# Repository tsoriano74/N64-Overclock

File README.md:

# N64 Switchless Overclock 🎮

Salut les bidouilleurs et les makers ! Voici le petit PCB d’overclock que j’ai réalisé pour ma Nintendo 64 custom. Il utilise un **ATtiny45** et le firmware **ManCloud**, avec le bouton RESET pour sélectionner le mode et une LED bicolore pour le repérer.

Je partage les sources KiCad, les fichiers de fabrication, les photos et surtout la méthode de flash avec un **ESP32 utilisé comme programmateur ISP lent**. C’est ce qui nous a permis de contourner les soucis rencontrés avec l’adaptateur USBasp après le changement d’horloge de l’ATtiny.

## À quoi sert cette carte ?

L’**overclock**, c’est faire fonctionner le processeur de la console plus vite que son réglage habituel. Cela peut améliorer la fluidité de certains jeux, mais le résultat varie d’un jeu et d’une console à l’autre.

Le mot **switchless** signifie « sans interrupteur supplémentaire » : on utilise le bouton RESET déjà présent sur la N64 pour choisir le mode. La petite puce **ATtiny45** lit ce bouton et commande les signaux de sélection du processeur. Le programme qui lui dit quoi faire s’appelle le **firmware** ; ici, c’est celui de ManCloud.

### Comment changer de mode ?

1. Un appui court sert à réinitialiser la console, comme d’habitude.
2. Un appui long permet de changer le mode sélectionné, indiqué par la LED à deux couleurs.
3. Il faut ensuite **éteindre puis rallumer la console** pour appliquer le nouveau réglage.

Les nombres ×1,5 et ×2 sont des multiplicateurs de l’horloge de base. **×2 ne veut pas dire que la console devient deux fois plus rapide que d’origine** : son réglage habituel est déjà ×1,5.

### La version du programme utilisée

Le firmware choisi est la variante **ATtiny45, multiplicateur maximal ×2, LED à cathode commune**, compilée avec `make tiny45_CC`. Son fichier s’appelle `n64_overclock_t45_2_0X_CC.hex`. Un appui court conserve la fonction RESET ; un appui long fait défiler les modes. Après sélection, il faut **éteindre puis rallumer la console** pour appliquer le multiplicateur, comme l’indique [ManCloud](https://github.com/ManCloud/n64_overclock).

Le mode standard est ×1,5 et l’autre mode est ×2. Les performances et la stabilité dépendent de la console, de son refroidissement et du jeu. La couleur de la LED indique un choix ; pour confirmer la vitesse réellement obtenue, il faut une mesure ou un test de performances (un « benchmark »).

## La carte

## Programmer la carte : commencez ici

**Flasher** signifie copier un programme dans une puce. Il y a ici deux programmes différents :

| Programme | Où le charger ? | À quoi sert-il ? |
|---|---|---|
| Le sketch `ESP32_AVR_ISP.ino` | Dans l’ESP32, avec Arduino IDE | Transformer l’ESP32 en outil pour programmer l’ATtiny |
| Le firmware ManCloud au format `.hex` | Dans l’ATtiny45 de la carte overclock | Faire fonctionner le mod une fois installé dans la N64 |

Pendant la programmation, le chemin est : **ordinateur → câble USB → ESP32 → six fils → carte overclock**. L’ESP32 sert seulement à préparer la carte : il ne reste pas dans la console.

👉 **[Guide complet : Arduino IDE, ESP32, câblage, AVRDUDE et fusibles](docs/FLASH-ESP32.md)**

Le **sketch** (programme Arduino) [pour l’ESP32](programming/ESP32_AVR_ISP/ESP32_AVR_ISP.ino) a été retrouvé dans le fichier utilisé pour le projet. Il utilise **STK500v1**, le langage attendu par l’outil de transfert, à **19 200 bauds**. Il envoie les données à l’ATtiny avec une horloge lente d’environ **10 kHz**, adaptée à son réglage. Ces nombres sont déjà renseignés dans le guide et le sketch. Le guide distingue bien le firmware à charger dans l’ATtiny du sketch à charger dans l’ESP32.

**La dernière étape change le rôle d’une patte de l’ATtiny pour que le bouton RESET puisse servir au mod. Ensuite, on ne peut plus reprogrammer la puce avec ce même branchement ESP32.** C’est le réglage `HFUSE = 0x5F` : il faut le faire uniquement à la fin, après toutes les vérifications. Le guide explique cet ordre et la méthode particulière nécessaire pour revenir en arrière.

## Repères du PCB

Les **pastilles** sont les petites surfaces métalliques où souder les fils. Les inscriptions blanches sur la carte sont la **sérigraphie**. Le tableau ci-dessous indique où vont ces pastilles dans les fichiers KiCad fournis.

- **GND** : la masse, le point commun de référence électrique du montage.
- **3,3 V** : l’alimentation de la carte pendant la programmation.
- **MOSI, MISO et SCK** : les trois fils utilisés pour échanger les données de programmation.
- **RST / RESET** : le fil qui permet au programmateur de prendre le contrôle de la puce.
- **Broche** : une patte physique du composant ; **PB0, PB1…** sont les noms que lui donne le fabricant.

Pour relier l’ESP32, utilisez le [tableau de câblage du guide](docs/FLASH-ESP32.md#3-câbler-esp32--pcb-overclock), qui donne aussi les numéros des GPIO. Ne vous servez pas du tableau ci-dessous pour deviner ces numéros.

| Repère du PCB | Connexion ATtiny45 | Rôle |
|---|---|---|
| `1/RST` | Broche 1, PB5 | RESET pendant la programmation |
| `5/MOSI` | Broche 5, PB0 | MOSI pendant la programmation |
| `6/MISO` | Broche 6, PB1 | MISO pendant la programmation |
| `7/SCK` | Broche 7, PB2 | SCK pendant la programmation |
| `4/GND` | Broche 4 | Masse |
| `TP6`, sérigraphie `8/3.3V` | Broche 8 | Alimentation 3,3 V |
| J2, `RIN` / `R_IN` | Broche 1 | Entrée côté bouton RESET |
| J3, `ROUT` / `R_OUT` | Broche 5 | Sortie RESET côté console |
| J4, `112` | Broche 6 | Raccordement CPU 112 |
| J5, `116` | Broche 7 | Raccordement CPU 116 |
| J7, `L1` / `LED_R` | Broche 2 via R2, 100 Ω | Première couleur de LED |
| J8, `L2` / `LED_Y` | Broche 3 via R1, 100 Ω | Deuxième couleur de LED |

Une LED bicolore contient deux couleurs et peut avoir une patte commune. La variante **CC** signifie « cathode commune » : cette patte commune doit être reliée au GND. Vérifiez le type de votre LED avant de choisir le firmware. Les noms `LED_R` et `LED_Y` ne déterminent pas la couleur de la LED réellement montée. Sur mon montage, L1 était vert et L2 rouge.

Pour installer le RESET, il faut distinguer les côtés bouton et PIF : **RIN et ROUT ne doivent pas simplement être raccordés à deux points d’une même piste restée continue**. Les anciens échanges identifiaient ROUT vers le PIF-NUS 27. La coupure ou l’isolation exacte dépend de la carte mère : se référer aux photos d’installation adaptées à sa révision avant de modifier les pistes. Voir les [références et vérifications](docs/REFERENCES.md).

## Fabriquer la carte ou modifier le projet

Pour récupérer le projet, cliquez sur **Code → Download ZIP** en haut du dépôt, puis décompressez le fichier sur votre ordinateur.

- Pour **faire fabriquer le circuit imprimé**, le fabricant utilise les fichiers **Gerber** et de perçage contenus dans `production/N64_overclock.zip`.
- Pour **faire monter les composants**, il utilise aussi la **BOM** (liste des composants) et le fichier **positions** (endroit et sens de chaque composant).
- Pour **modifier la carte**, ouvrez le fichier `.kicad_pro` du dossier `hardware` avec KiCad, le logiciel de conception électronique.

La programmation de l’ATtiny et la soudure dans la console sont encore à faire après la fabrication. Les photos de ce dépôt montrent le petit PCB assemblé ; elles ne montrent pas tous les points de soudure d’une installation dans la N64. Avant de modifier la console, il faut un repérage adapté à la version de sa carte mère.

### Où trouver chaque fichier ?

| Dossier ou fichier | Contenu |
|---|---|
| `hardware/` | Projet, schéma et PCB KiCad originaux |
| `production/N64_overclock.zip` | Gerbers et perçages fournis |
| `production/bom.csv` | Liste des composants ; références catalogue LCSC à compléter |
| `production/positions.csv` | Positions originales de placement |
| `programming/ESP32_AVR_ISP/` | Sketch du programmateur ESP32 pour Arduino IDE |
| `docs/FLASH-ESP32.md` | Procédure de flash et dépannage |
| `docs/REFERENCES.md` | Provenance, sources et limites des vérifications |
| `docs/images/` | Schéma, rendu, tracé et photos |
| `SOURCE-SHA256.txt` | Codes de contrôle pour vérifier que les fichiers sont restés identiques |

Les seuls composants à assembler sont **U1 (ATtiny45 SOIC-8), C1 (100 nF) et R1/R2 (100 Ω)**. Les six points de test et J1 à J8 sont des pastilles, pas des pièces à acheter. Si le fabricant les indique comme non assemblés, c’est attendu uniquement pour ces repères. Les références **LCSC** sont les numéros du catalogue de composants utilisé pour l’assemblage JLCPCB. Elles sont vides dans cette BOM : il faut encore choisir les bonnes pièces avant de commander une carte assemblée. Cette BOM n’est donc pas une commande prête à valider sans vérification.

## Crédits

- [ManCloud — n64_overclock](https://github.com/ManCloud/n64_overclock) : firmware AVR. Le source porte une licence **GPL-2.0-only**.
- [borti4938 — N64 Switchless Overclock](https://github.com/borti4938/N64_Switchless_Overclock) : projet à l’origine du port AVR.
- [Consoles Unleashed — Nintendo 64 Switchless Overclock PCB](https://github.com/consolesunleashed/nintendo-64-switchless-overclock-pcb) : référence de PCB citée dans les échanges de conception.

Le firmware ManCloud est récupéré depuis son dépôt d’origine, à une révision précise indiquée dans le guide. Aucune nouvelle licence globale n’est imposée aux fichiers matériels ou au sketch récupéré ; leur provenance et leurs droits restent à distinguer. Projet indépendant, sans affiliation avec Nintendo.

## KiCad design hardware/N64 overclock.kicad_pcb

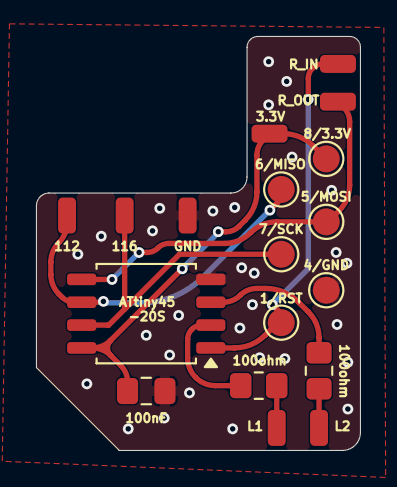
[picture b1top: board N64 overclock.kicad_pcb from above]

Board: 2 copper layers, 18.0 x 23.0 mm, 18 parts (0 on the bottom side), 10 nets.

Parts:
1/RST, 4/GND, 5/MOSI, 6/MISO, 7/SCK: TestPoint; TestPoint_Pad_D1.5mm
C1: 100nF; C_0805_2012Metric_Pad1.18x1.45mm_HandSolder
J1: 3.3V_PAD; SolderWirePad_1x01_SMD_1x2mm
J2: RIN; SolderWirePad_1x01_SMD_1x2mm
J3: ROUT; SolderWirePad_1x01_SMD_1x2mm
J4: CPU112; SolderWirePad_1x01_SMD_1x2mm
J5: CPU116; SolderWirePad_1x01_SMD_1x2mm
J6: GND_PAD; SolderWirePad_1x01_SMD_1x2mm
J7: LED_R; SolderWirePad_1x01_SMD_1x2mm
J8: LED_Y; SolderWirePad_1x01_SMD_1x2mm
R1, R2: 100; R_0805_2012Metric_Pad1.20x1.40mm_HandSolder
TP6: TestPoint; TestPoint_Pad_D1.5mm
U1: ATtiny45-20S; SOIC-8_5.3x5.3mm_P1.27mm

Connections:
+3.3V: C1.1, J1.1 (Pin_1_1), TP6.1 (1_1), U1.8 (VCC)
GND: 4/GND.1 (1_1), C1.2, J6.1 (Pin_1_1), U1.4 (GND)
MISO: 6/MISO.1 (1_1), J4.1 (Pin_1_1), U1.6 (PB1)
MOSI: 5/MOSI.1 (1_1), J3.1 (Pin_1_1), U1.5 (AREF/PB0)
unnamed: J7.1 (Pin_1_1), R2.2
unnamed: J8.1 (Pin_1_1), R1.2
unnamed: R2.1, U1.2 (XTAL1/PB3)
unnamed: R1.1, U1.3 (XTAL2/PB4)
RESET: 1/RST.1 (1_1), J2.1 (Pin_1_1), U1.1 (~RESET/PB5)
SCK: 7/SCK.1 (1_1), J5.1 (Pin_1_1), U1.7 (PB2)

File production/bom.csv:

Designator,Footprint,Quantity,Value,LCSC Part #
"1/RST, 4/GND, 5/MOSI, 6/MISO, 7/SCK, TP6",TestPoint_Pad_D1.5mm,6,TestPoint,
C1,0805,1,100nF,
J1,SolderWirePad_1x01_SMD_1x2mm,1,3.3V_PAD,
J2,SolderWirePad_1x01_SMD_1x2mm,1,RIN,
J3,SolderWirePad_1x01_SMD_1x2mm,1,ROUT,
J4,SolderWirePad_1x01_SMD_1x2mm,1,CPU112,
J5,SolderWirePad_1x01_SMD_1x2mm,1,CPU116,
J6,SolderWirePad_1x01_SMD_1x2mm,1,GND_PAD,
J7,SolderWirePad_1x01_SMD_1x2mm,1,LED_R,
J8,SolderWirePad_1x01_SMD_1x2mm,1,LED_Y,
"R1, R2",0805,2,100,
U1,SOIC-8_5.3x5.3mm_P1.27mm,1,ATtiny45-20S,
